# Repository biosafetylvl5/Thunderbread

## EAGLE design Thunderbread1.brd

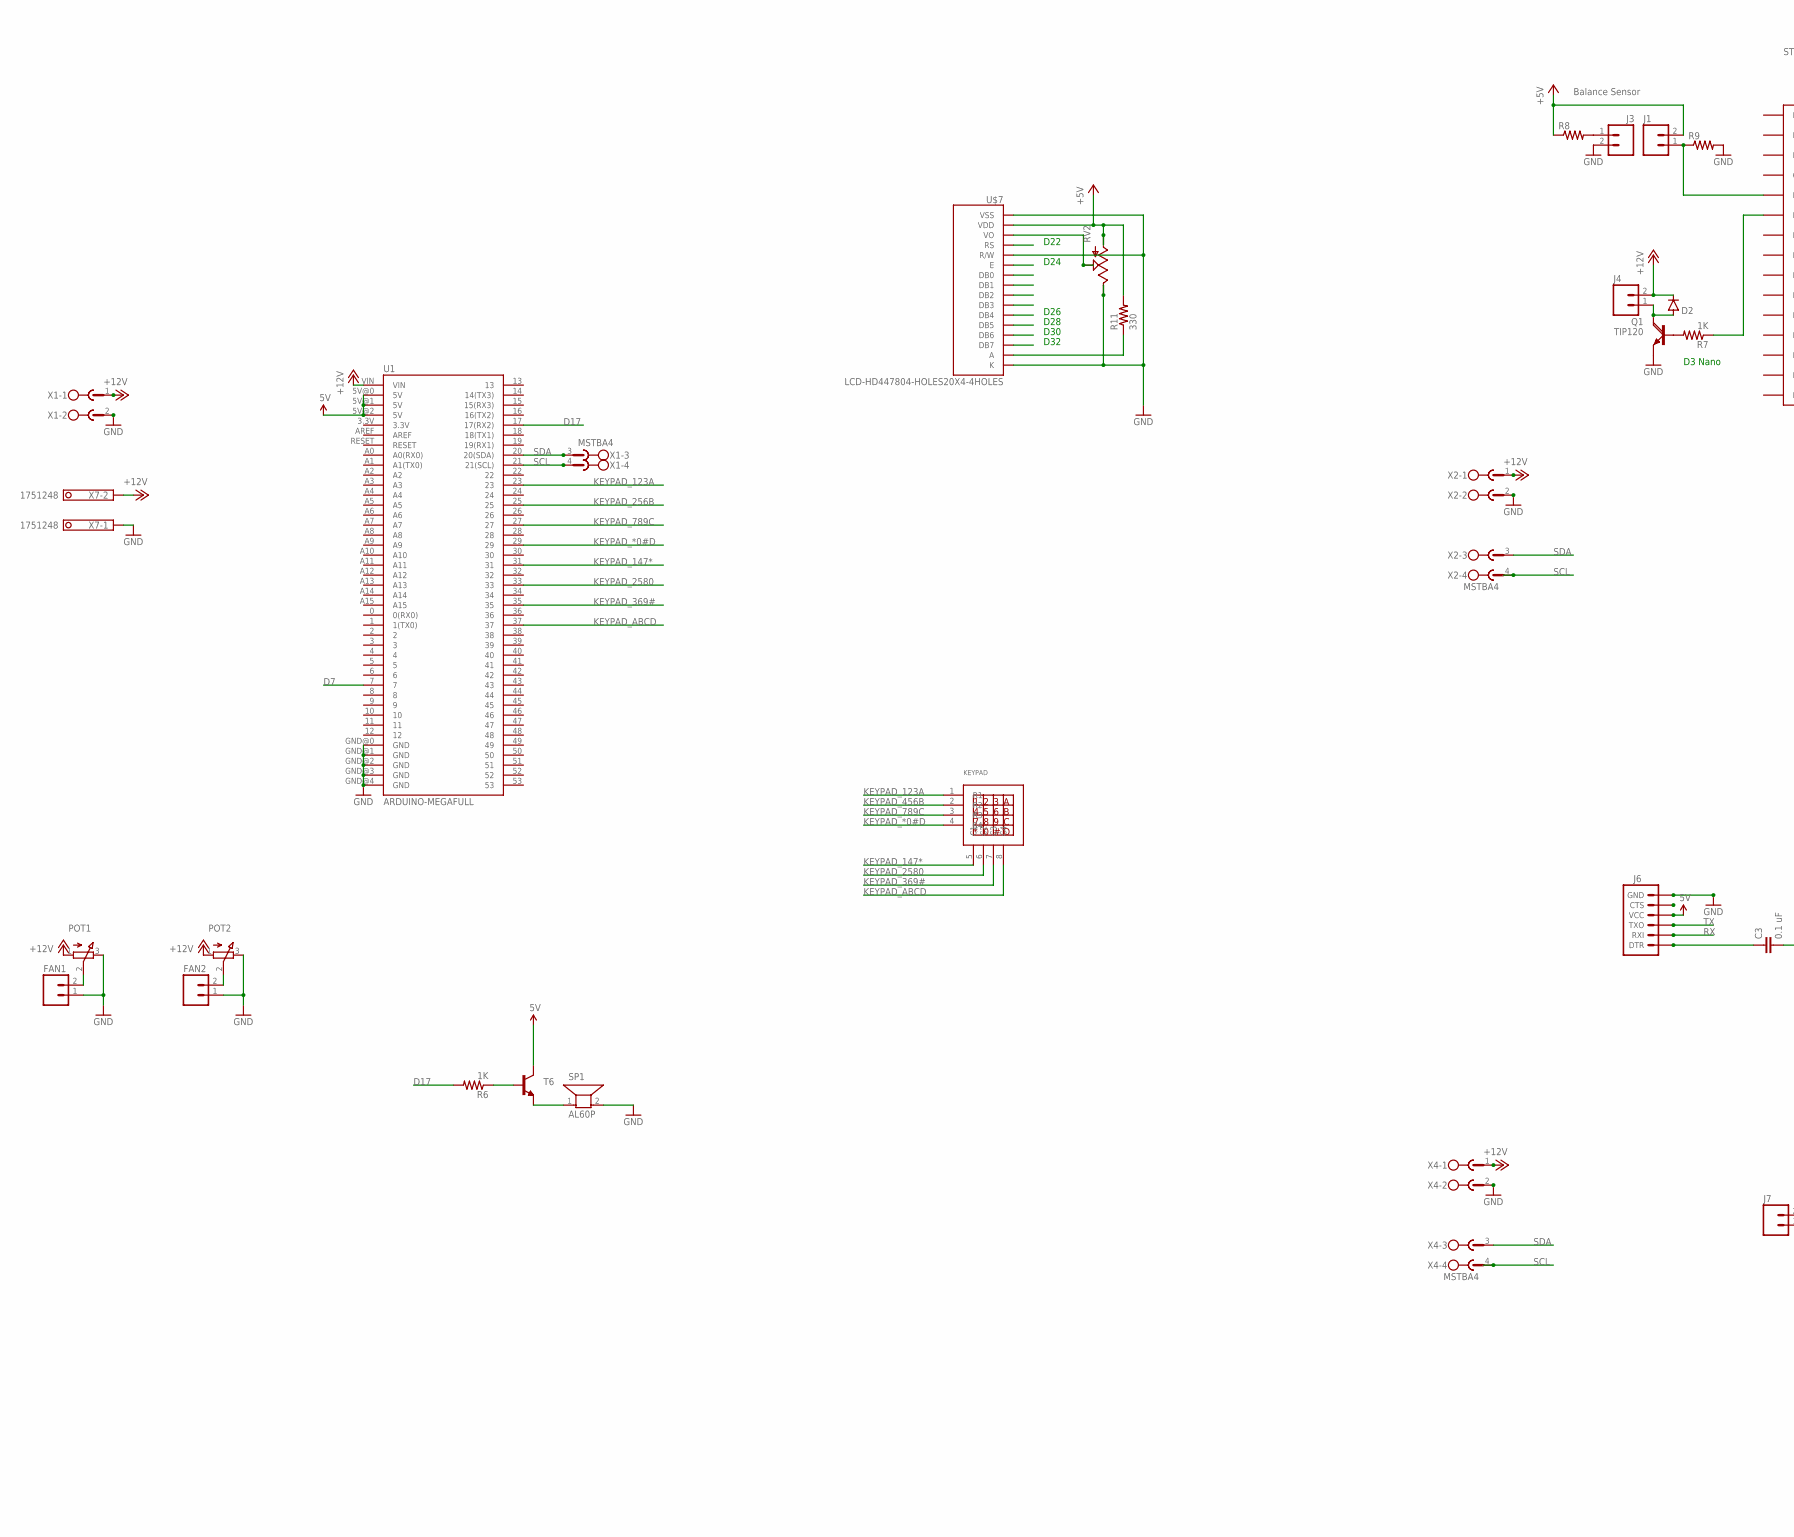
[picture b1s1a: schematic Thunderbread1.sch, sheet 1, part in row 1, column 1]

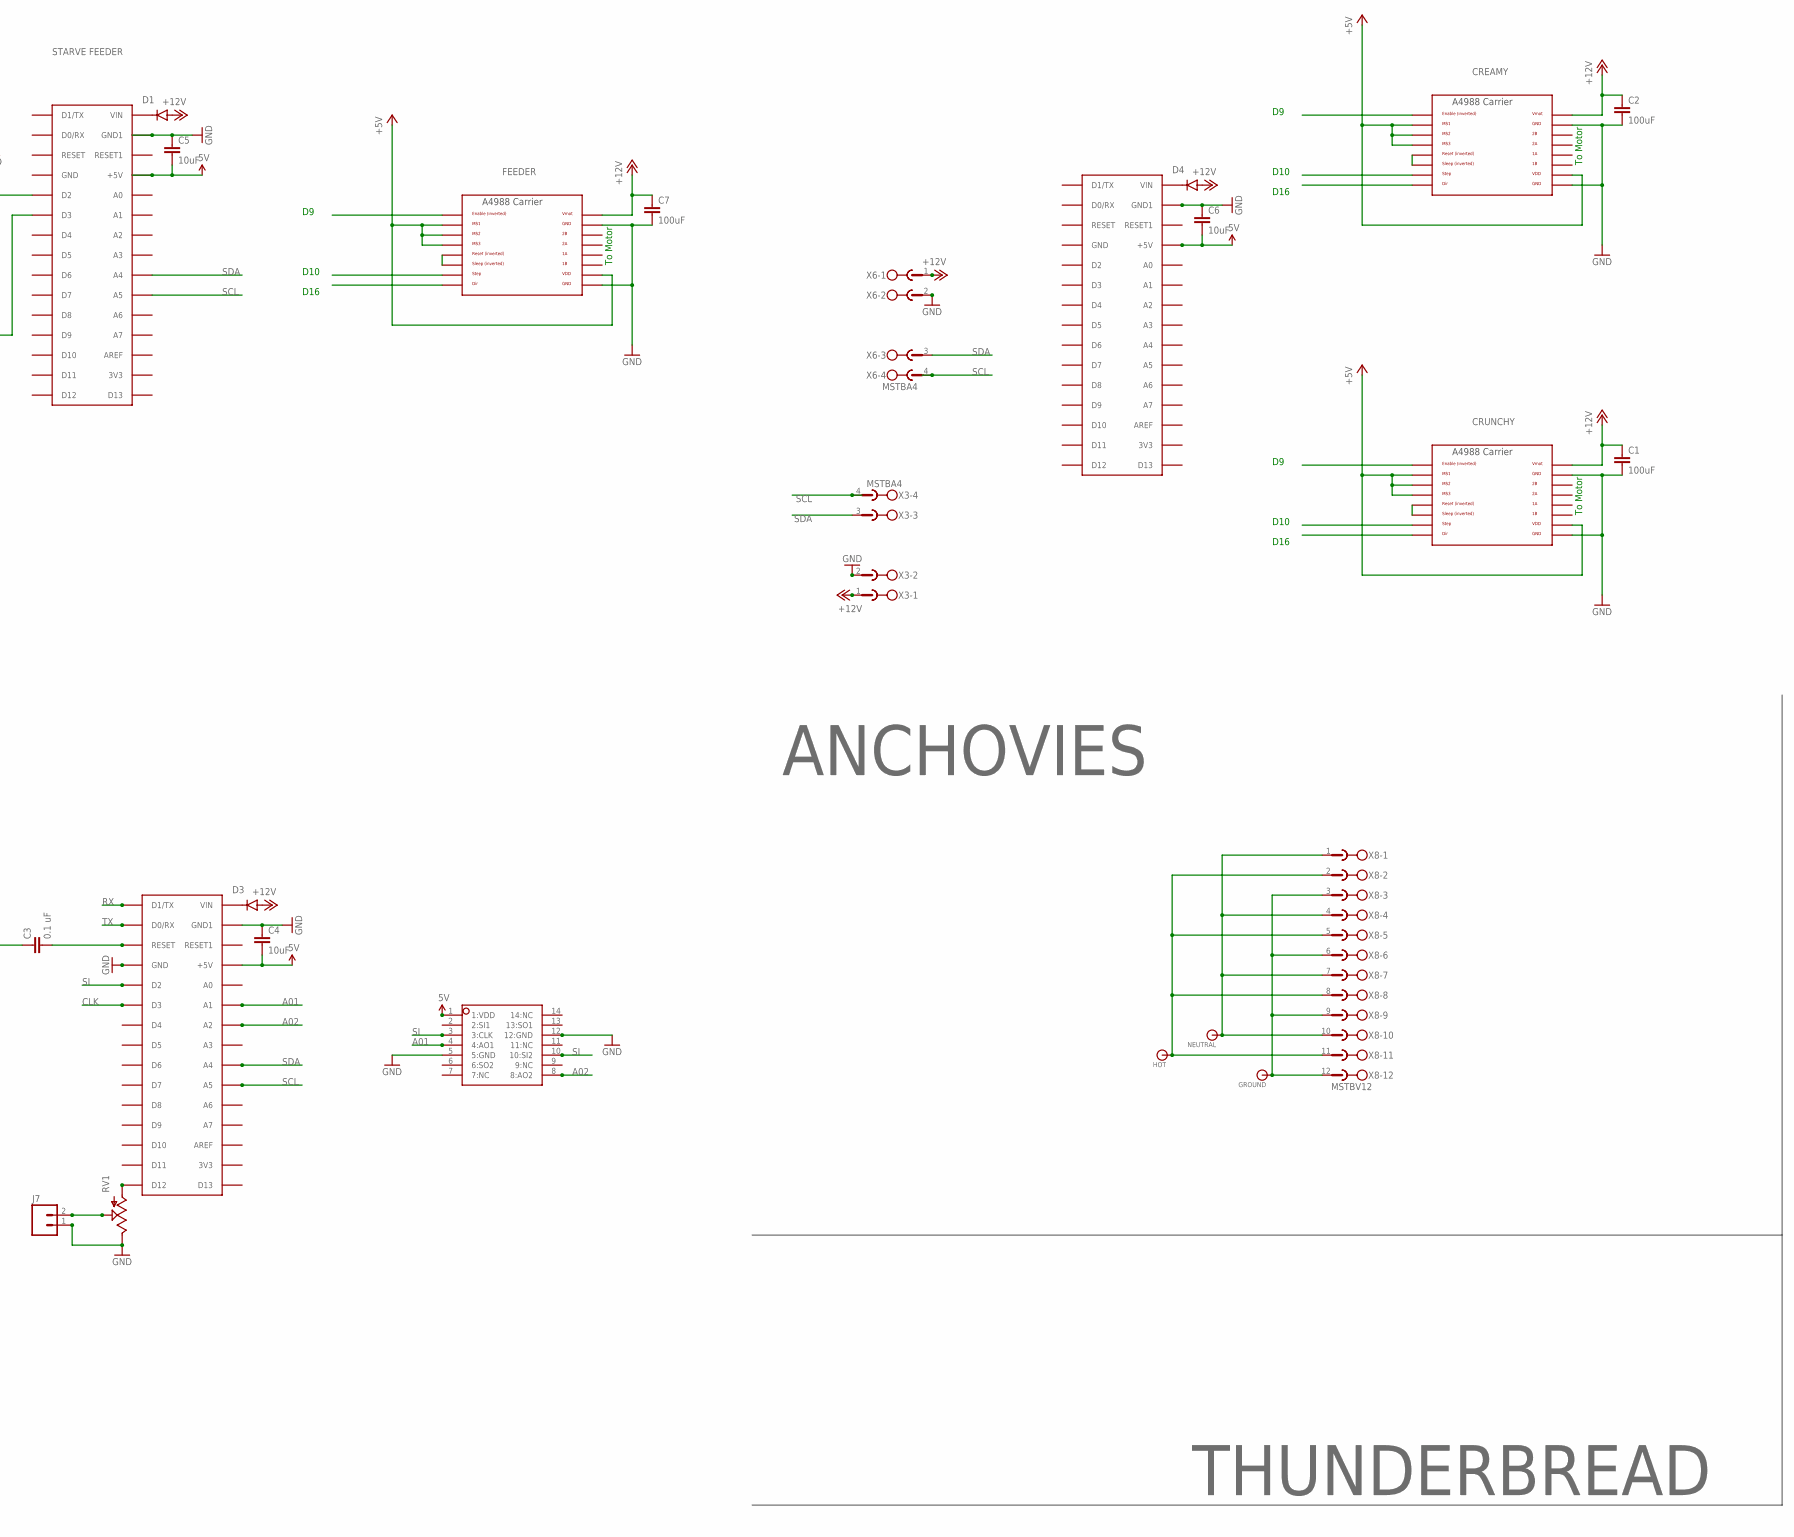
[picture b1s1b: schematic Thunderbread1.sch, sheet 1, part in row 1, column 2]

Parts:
C1, C2, C7: 100uF; 1210
C3: 0.1 uF; CAP-PTH-SMALL-KIT
C4, C5, C6: 10uF; 1206
D1, D2, D3, D4: DIODESMA; SMA-DIODE
FAN1, FAN2: M02LOCK_LONGPADS; 1X02_LOCK_LONGPADS
GROUND: BANANA_CONN
HOT: BANANA_CONN
J1, J3, J4, J7: M02LOCK; 1X02_LOCK
J6: ARDUINO_SERIAL_PROGRAMLOCK; 1X06_LOCK
KEYPAD: KEYPAD4X4
NEUTRAL: BANANA_CONN
POT1, POT2: 3RP/1610N
Q1: TIP120; TO220AH
R6, R7: 1K; AXIAL-0.3
R8, R9: RESISTOR1206; 1206
R11: 330; 1206
RV1, RV2: POTTRIM; TRIM_POT
SP1: AL60P
T6: TRANSISTOR_NPNBC547; TO-92-AMMO
U1: ARDUINO-MEGAFULL; ARDUINO_MEGA
U$1, U$2, U$8: ARDUINONANO; PDIP-32
U$3, U$4, U$6: POLOLU_A4983CARRIER; A4988BREAKOUT
U$5: TSL1402R
U$7: LCD-HD447804-HOLES20X4-4HOLES; LCD-20X4-4HOLES
X1, X2, X3, X4, X6: MSTBA4
X7: 1751248
X8: MSTBV12

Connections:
5V: C4.2, C5.2, C6.2, J6.4 (VCC), T6.1 (C), U1.5V@0 (5V), U1.5V@1 (5V), U1.5V@2 (5V), U$1.+5V, U$2.+5V, U$5.1 (1:VDD), U$8.+5V; also elsewhere on the board
+5V: J1.2, R8.1, R11.2, RV2.3 (A), U$3.MS1, U$3.MS2, U$3.MS3, U$3.VDD, U$4.MS1, U$4.MS2, U$4.MS3, U$4.VDD, U$6.MS1, U$6.MS2, U$6.MS3, U$6.VDD, U$7.P$2 (VDD)
+12V: C1.1, C2.1, C7.1, D1.A, D2.C, D3.A, D4.A, J4.2, POT1.1 (A), POT2.1 (A), U1.VIN, U$3.VMOT, U$4.VMOT, U$6.VMOT, X1.1, X2.1, X3.1, X4.1, X6.1, X7.2
A01: U$1.A1, U$5.4 (4:AO1)
A02: U$1.A2, U$5.8 (8:AO2)
CLK: U$1.D3
D7: U1.7; also elsewhere on the board
D17: R6.P$2 (2), U1.17 (17(RX2))
GND: C1.2, C2.2, C4.1, C5.1, C6.1, C7.2, FAN1.1, FAN2.1, J3.2, J6.6 (GND), J7.1, POT1.3 (E), POT2.3 (E), Q1.E, R9.2, RV1.2 (E), RV2.2 (E), SP1.2, U1.GND@0 (GND), U1.GND@1 (GND), U1.GND@2 (GND), U1.GND@3 (GND), U1.GND@4 (GND), U$1.GND, U$1.GND1, U$2.GND1, U$3.GND, U$3.GND@0 (GND), U$4.GND, U$4.GND@0 (GND), U$5.5 (5:GND), U$5.12 (12:GND), U$6.GND, U$6.GND@0 (GND), U$7.P$1 (VSS), U$7.P$5 (R/W), U$7.P$16 (K), U$8.GND1, X1.2, X2.2, X3.2, X4.2, X6.2, X7.1; also elsewhere on the board
KEYPAD_123A: KEYPAD.1 (R1), U1.23
KEYPAD_147*: KEYPAD.5 (C1), U1.31
KEYPAD_256B: U1.25
KEYPAD_369#: KEYPAD.7 (C3), U1.35
KEYPAD_456B: KEYPAD.2 (R2)
KEYPAD_789C: KEYPAD.3 (R3), U1.27
KEYPAD_2580: KEYPAD.6 (C2), U1.33
KEYPAD_*0#D: KEYPAD.4 (R4), U1.29
KEYPAD_ABCD: KEYPAD.8 (C4), U1.37
unnamed: J3.1, R8.2
unnamed: J1.1, R9.1, U$2.D2
unnamed: D2.A, J4.1, Q1.C
unnamed: R7.P$1 (1), U$2.D3
unnamed: Q1.B, R7.P$2 (2)
unnamed: FAN1.2, POT1.2 (S)
unnamed: FAN2.2, POT2.2 (S)
unnamed: D1.C, U$2.VIN
unnamed: C3.2, U$1.RESET
unnamed: U$3.RST, U$3.SLP (SLEEP)
unnamed: U$4.RST, U$4.SLP (SLEEP)
unnamed: D4.C, U$8.VIN
unnamed: RV1.3 (A), U$1.D12
unnamed: C3.1, J6.1 (DTR)
unnamed: J7.2, RV1.1 (S)
unnamed: U$6.RST, U$6.SLP (SLEEP)
unnamed: R6.P$1 (1), T6.2 (B)
unnamed: SP1.1, T6.3 (E)
unnamed: HOT.P$1, X8.2, X8.5, X8.8, X8.11
unnamed: NEUTRAL.P$1, X8.1, X8.4, X8.7, X8.10
unnamed: GROUND.P$1, X8.3, X8.6, X8.9, X8.12
unnamed: RV2.1 (S), U$7.P$3 (VO)
unnamed: R11.1, U$7.P$15 (A)
unnamed: D3.C, U$1.VIN
RX: J6.2 (RXI), U$1.D1/TX
SCL: U1.21 (21(SCL)), U$1.A5, U$2.A5, X2.4, X3.4, X4.4, X6.4
SDA: U1.20 (20(SDA)), U$1.A4, U$2.A4, X2.3, X3.3, X4.3, X6.3
SI: U$1.D2, U$5.3 (3:CLK), U$5.10 (10:SI2)
TX: J6.3 (TXO), U$1.D0/RX

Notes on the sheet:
STARVE FEEDER
Balance Sensor
D3 Nano
To Motor
CRUNCHY
D10
D16
CREAMY
FEEDER
ANCHOVIES
D22
D24
D26
D28
D30
D32
THUNDERBREAD

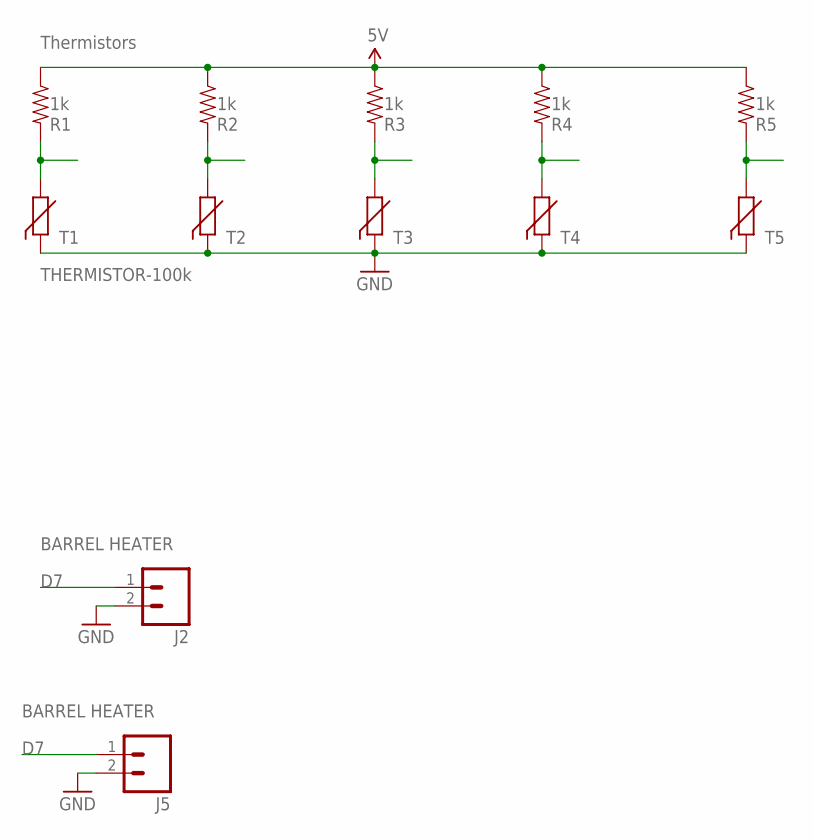
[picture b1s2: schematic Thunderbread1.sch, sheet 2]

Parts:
J2, J5: M02LOCK; 1X02_LOCK
R1, R2, R3, R4, R5: 1k; 1206
T1, T2, T3, T4, T5: THERMISTOR-100k; RS-2,5

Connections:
5V: R1.1, R2.1, R3.1, R4.1, R5.1; also elsewhere on the board
D7: J2.1, J5.1; also elsewhere on the board
GND: J2.2, J5.2, T1.1, T2.1, T3.1, T4.1, T5.1; also elsewhere on the board
unnamed: R1.2, T1.2
unnamed: R2.2, T2.2
unnamed: R3.2, T3.2
unnamed: R4.2, T4.2
unnamed: R5.2, T5.2

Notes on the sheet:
Thermistors
BARREL HEATER

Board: 2 copper layers, 62 parts (0 on the bottom side), 49 nets, no tracks yet.

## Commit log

2016-09-05 Initial commit :purple_heart: - initial work done by Maaphoo
2016-09-05 Diameter sensor & starve feeder rewired
2016-09-05 Clean slate
2016-09-05 Added keypad

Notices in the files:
parts and their libraries:
SparkFun-DiscreteSemi: Licensing: Creative Commons ShareAlike 4.0 International - https://creativecommons.org/licenses/by-sa/4.0
